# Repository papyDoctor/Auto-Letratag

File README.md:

# Auto-Letratag

**📖 Build log, photos and videos: [papydoctor.github.io/Auto-Letratag](https://papydoctor.github.io/Auto-Letratag/)**

Also published on [Hackster.io](https://www.hackster.io/papyDoctor/auto-letratag-batch-printing-and-cutting-of-numbered-labels-c18717).

This project is a reverse engineering of the LetraTag LT‑100H, a 12 mm label printer. I built it for my own needs, to automate label making. I have thousands of 12 mm labels to print with increasing numbers, and I no longer wanted to do it by hand on the LT‑100H. As far as I know, there is no device that can print series of 12 mm labels with automatic cutting.

The system connects to a PC through its USB‑C port, which both powers the printer and controls it.

In practice, this project needs an LT‑100H and:

| Function | Part |
|---|---|
| Microcontroller | Waveshare RP2350‑Zero (RP2350A, USB‑C) |
| Motor | NEMA 17 17HS19‑1684D, directly on the original roller |
| Motor driver | Watterott TMC2209 SilentStepStick, 1/32 microstepping, stealthChop, about 0.4 A |
| Head and motor supply | TPS61089 boost converter, 5 V → 6.5 V, enabled by the firmware |
| Head driver | 4 × TLC5916 in a daisy chain, used as switches: the head runs at constant voltage (about 73 mA per dot) |
| Cutter | HS-5085MG servo |
| User interface | 2 buttons, VBUS and head rail sensing, input for an optional thermistor |

All of the original electronics are replaced by a custom board. The thermal print head, the drive roller, the blade and the tape cassettes come from the original machine. The board drives a stepper motor coupled directly to the roller and cuts the tape with a servo. A terminal program lays out the text and sends it to the printer.

Terminal features:

- **Numbered series.** The template `BOX-{n:03}` from 1 to 20 gives BOX-001, BOX-002, … BOX-020.
- **Chained labels.** Labels are printed back to back. Each one is cut when its boundary reaches the blade, so no tape is wasted between labels.
- **Continuous printing** at about 30 mm/s: the motor does not stop between lines.
- **Full-height text** using all 30 dots of the head, on one or more lines, in any TrueType font.
- **Saved templates** to quickly reuse frequent texts.

The 3D model of the assembly is in [`mechanical/ASSY.glb`](mechanical/ASSY.glb).

> This is a personal project, I'm not affiliated with Dymo. Dymo and LetraTag are trademarks of their respective owners.

## Specifications

| | |
|---|---|
| Print head | 30 dots, 0.15 mm pitch (about 170 dpi), 4.5 mm print height |
| Speed | about 30 mm/s in continuous mode (5 ms per full line) |
| Cutting | automatic, servo-driven, head-to-blade distance adjustable without recompiling |
| Power | USB‑C 5 V (designed for a USB‑C port that supplies up to 3 A) |
| Link | USB serial port, text protocol |

## V3 board

KiCad 10, 4-layer, 70 × 60 mm ([`hardware/V3`](hardware/V3), schematic as [PDF](hardware/V3/letratag-schematic.pdf)).

**Head drive.** The head and motor rail (+6V5 in the schematic) is set to 6.5 V. Each TLC5916 output only switches its dot on and off; its current limit, about 105 mA with R1–R4 = 180 Ω, only protects the head. The board was first built to drive the dots at constant current (7.5 V rail, 69 mA per dot). That was a mistake: the resistance of a dot rises as it wears, and at constant current its power (I²R) rises with it, so a worn dot runs hotter and hotter until it burns out. At constant voltage, its power (V²/R) goes down instead.

**Heating time.** Each dot heats for 1.5 ms, a constant in the firmware (`HEAT_US`), not a setting. At 6.5 V, 1.5 ms already prints solid black and 1 ms prints grey; longer pulses only wear the head.

**Current budget.** Heating all 30 dots at once would draw about 3.2 A from USB. The firmware therefore heats each line in groups of 10 dots. The groups are interleaved, so the text stays straight while the tape moves.

**Power sequencing.** The switched +5 V rail comes up first, then the head and motor rail, then the motor driver. Everything is switched off at the end of a series, or after one minute without activity.

[`hardware/V1`](hardware/V1) and [`hardware/V2`](hardware/V2) are earlier versions, built around a XIAO RP2350 and the original DC motor.

## Firmware

[`firmware/letratag_v3/letratag_v3.ino`](firmware/letratag_v3/letratag_v3.ino), written in Arduino.

To build it, install Earle Philhower's [arduino‑pico](https://github.com/earlephilhower/arduino-pico) core in the Arduino IDE and select the **Waveshare RP2350 Zero** board. The `Servo` and `EEPROM` libraries come with the core. From the command line:

```sh
arduino-cli compile --fqbn rp2040:rp2040:waveshare_rp2350_zero firmware/letratag_v3
```

The folder also contains two other programs:
- [`firmware/test_v3`](firmware/test_v3): a bring-up sketch for the V3 board, to test the power rails, motor, servo and head one at a time;
- [`firmware/letratag`](firmware/letratag): the firmware for the earlier versions.

### Console

The USB serial port runs at 115200 baud, with newline line endings. `help` (or any unknown command) lists all commands.

| Command | Action |
|---|---|
| `blocks`, `ruler`, `square`, `line <dot>`, `dots` | test labels (`dots`: staircase to find a dead dot) |
| `blade <mm>` | distance from the dot line to the blade (saved in flash) |
| `margin <mm>` | blank space before and after the text (saved in flash) |
| `group <n>` | number of dots heated at the same time (saved in flash) |
| `calib` | prints a thin bar and cuts through its middle if `blade` is right |
| `feed <mm>`, `cut`, `flush` | feed the tape; cut; feed out and cut what has been printed |
| `status`, `off` | voltages and settings; switch off all power rails |

**Buttons:**
- **A**, held: feeds the tape;
- **B**: cuts what has been printed;
- **either button** stops a print in progress.

### Cutter calibration

Do this once, then again whenever the cutter mechanism changes:

1. Type `calib`. The firmware prints a thin bar and cuts where its middle should be.
2. Look for the bar:
   - **on the piece that came out**, x mm from the edge: type `blade <current value − x>`;
   - **on the tape still in the machine**, x mm from the edge: type `blade <current value + x>`.
3. Repeat until the cut goes through the bar.

The cutter servo travel is set in the firmware by `SERVO_REST_US` (blade retracted) and `SERVO_CUT_US` (full cut). Measure it on each mechanism: beyond these limits, the servo pushes against its end stops.

### Protocol

One text command per line:

```
PC → INFO                     PC ← INFO first=1 dots=30 pitch_um=150 max_lines=4000 cut=2
PC → IMG <n> [c] [k]          PC ← READY <n>
PC → L <hex>   (n times)      PC ← P <i>/<n> … SPEED … VOLTAGES … DONE
PC → FLUSH                    PC ← DONE
```

- **`L` lines:** each line is a 30-bit word in hexadecimal; bit 0 is the top dot of the label.
- **`c`:** `1` (default) for continuous printing, `0` to stop the motor at each line.
- **`k`:** `1` (default) to feed out and cut the label, `0` if another label follows. In that case, the cut happens while the next label is printing.
- **`ERR <message>`** reports an error.

## Terminal program

[`software`](software) is a terminal application written in Rust with ratatui.

```sh
cd software
cargo build --release
./target/release/letratag
```

The program finds the board on USB by itself. Close the Arduino IDE serial monitor first, otherwise the port is busy.

| Option | |
|---|---|
| `--port <port>` | serial port, if automatic detection fails |
| `--font <file.ttf>` | font (default: macOS Arial Bold) |
| `--width <factor>` | character width, from 1 to 2 (default 1.08, matching an original Dymo label) |
| `--templates <file>` | saved templates file (default: `~/.config/letratag/templates.txt`) |
| `--mirror` | prints the text mirrored |

**Fields:**
- **Template**: the text. `{n}` or `{n:03}` is replaced by the number, and `|` starts a new line.
- **Start** and **End**: the numbers of the series.

A preview shows the label before printing.

| Key | |
|---|---|
| Ctrl‑P or F5 | print the series |
| Ctrl‑N | new line in the template |
| Ctrl‑S / Ctrl‑O | save the template / pick a saved template |
| Ctrl‑A | continuous / stop at each line |
| Esc | stop after the current label, or quit |

Saved templates are stored in a plain text file, one per line, which can also be edited by hand.

## Repository layout

```
firmware/     V3 firmware, bring-up sketch, firmware for earlier versions
software/     PC program (Rust)
hardware/     V1, V2, V3 boards (KiCad)
mechanical/   3D assembly (ASSY.glb)
docs/         project web page (GitHub Pages)
Datasheets/   component datasheets
scripts/      helper tools
```

## License

Copyright (c) 2026 Olivier Monnom.

| | License |
|---|---|
| Software: `firmware/`, `software/`, `scripts/` | [MIT](LICENSE) |
| Hardware: `hardware/` (KiCad boards), `mechanical/` (3D parts) | [CERN-OHL-P v2](LICENSE-HARDWARE) |
| Documentation: `docs/` (text, photos, videos), this README | [CC BY 4.0](LICENSE-DOCS) |

Not covered by these licenses, and belonging to their manufacturers:
- the datasheets in `Datasheets/`;
- the vendor 3D models included in `mechanical/ASSY.glb`: stepper motor, servo, TMC2209 module.

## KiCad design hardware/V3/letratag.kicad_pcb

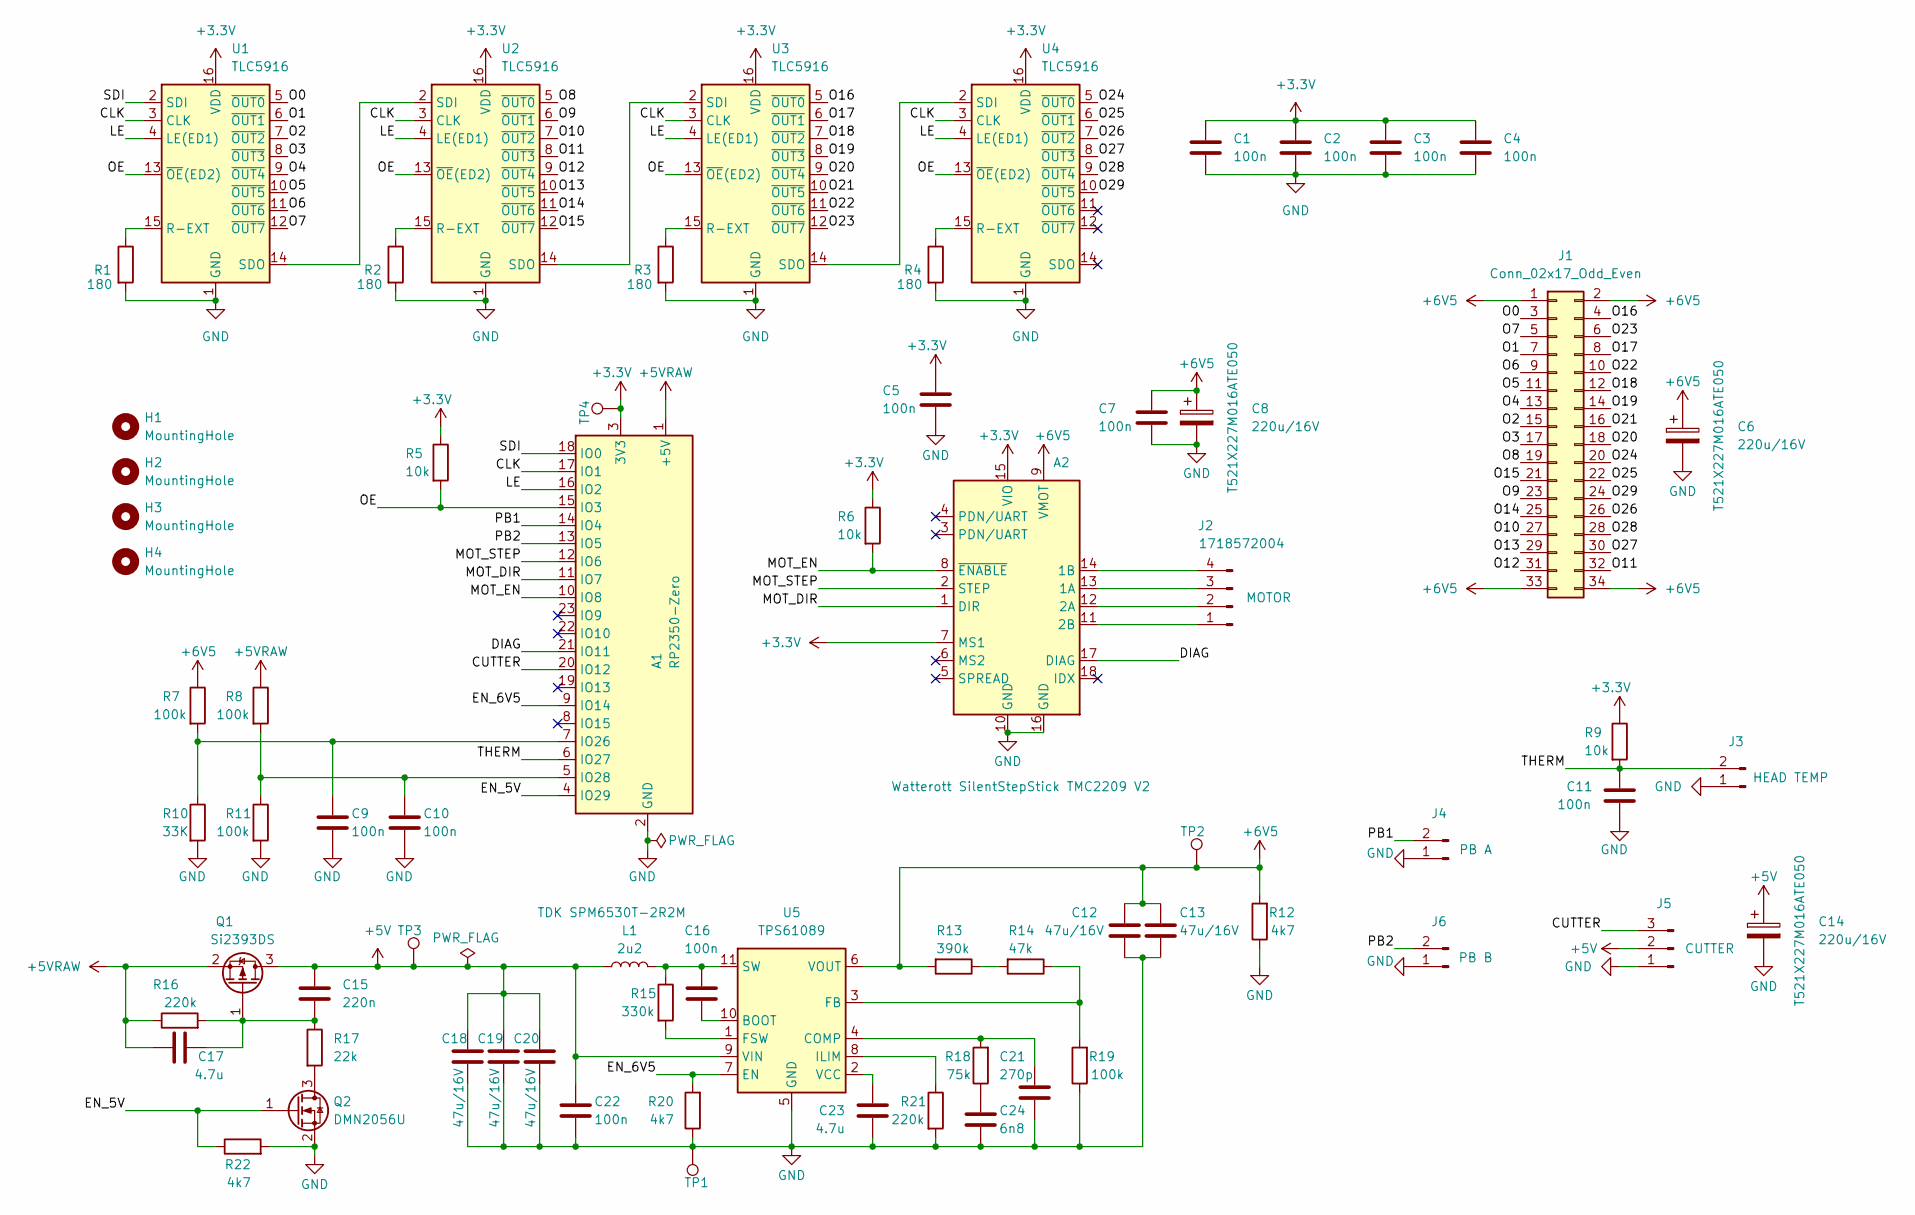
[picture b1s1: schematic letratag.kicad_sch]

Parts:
A1: RP2350-Zero; WAVESHARE-RP2350-ZERO
A2: Watterott SilentStepStick TMC2209 V2; Watterott_Breakout-16_15.2x20.3mm
C1, C2, C3, C4, C5, C7, C9, C10, C11, C16, C22: 100n; C_0603_1608Metric_Pad1.08x0.95mm_HandSolder
C6, C8, C14: 220u/16V; CP_EIA-7343-43_Kemet-X_HandSolder
C12, C13, C18, C19, C20: 47u/16V; C_1210_3225Metric_Pad1.33x2.70mm_HandSolder
C15: 220n; C_0603_1608Metric_Pad1.08x0.95mm_HandSolder
C17, C23: 4.7u; C_0603_1608Metric_Pad1.08x0.95mm_HandSolder
C21: 270p; C_0603_1608Metric_Pad1.08x0.95mm_HandSolder
C24: 6n8; C_0603_1608Metric_Pad1.08x0.95mm_HandSolder
H1, H2, H3, H4: MountingHole; MountingHole_3mm_Pad_Via
J1: Conn_02x17_Odd_Even; Samtec_EHF-117-01-L-D
J2: 1718572004; Molex_KK-254_RPC_1x04_P2.54mm_RA
J3: HEAD TEMP; JST_ZH_B2B-ZR_1x02_P1.50mm_Vertical
J4: PUSH BUTTON A; JST_ZH_B2B-ZR_1x02_P1.50mm_Vertical
J5: CUTTER; PinHeader_1x03_P2.54mm_Vertical
J6: PUSH BUTTON B; JST_ZH_B2B-ZR_1x02_P1.50mm_Vertical
L1: 2u2; L_TDK_SMP6530
Q1: Si2393DS; SOT-23
Q2: DMN2056U; SOT-23
R1, R2, R3, R4: 180; R_1206_3216Metric_Pad1.30x1.75mm_HandSolder
R5, R6, R9: 10k; R_0603_1608Metric_Pad0.98x0.95mm_HandSolder
R7, R8, R11, R19: 100k; R_0603_1608Metric_Pad0.98x0.95mm_HandSolder
R10: 33K; R_0603_1608Metric_Pad0.98x0.95mm_HandSolder
R12, R20, R22: 4k7; R_0603_1608Metric_Pad0.98x0.95mm_HandSolder
R13: 390k; R_0603_1608Metric_Pad0.98x0.95mm_HandSolder
R14: 47k; R_0603_1608Metric_Pad0.98x0.95mm_HandSolder
R15: 330k; R_0603_1608Metric_Pad0.98x0.95mm_HandSolder
R16, R21: 220k; R_0603_1608Metric_Pad0.98x0.95mm_HandSolder
R17: 22k; R_0603_1608Metric_Pad0.98x0.95mm_HandSolder
R18: 75k; R_0603_1608Metric_Pad0.98x0.95mm_HandSolder
TP1, TP2, TP3, TP4: TestPoint; TestPoint_THTPad_D2.0mm_Drill1.0mm
U1, U2, U3, U4: TLC5916; SOP-16_3.9x9.9mm_P1.27mm
U5: TPS61089; Texas_VQFN-RNR0011A-11

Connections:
+3.3V: A1.3 (3V3), A2.7 (MS1), A2.15 (VIO), C1.1, C2.1, C3.1, C4.1, C5.1, R5.1, R6.1, R9.1, TP4.1 (1_1), U1.16 (VDD), U2.16 (VDD), U3.16 (VDD), U4.16 (VDD)
+5V: C14.1, C15.1, C18.1, C19.1, C20.1, C22.1, J5.2, L1.1, Q1.3 (D), TP3.1 (1_1), U5.9 (VIN)
+5VRAW: A1.1 (+5V), C17.1, Q1.2 (S), R8.1, R16.1
+6V5: A2.9 (VMOT), C6.1, C7.1, C8.1, C12.1, C13.1, J1.1, J1.2, J1.33, J1.34, R7.1, R12.2, R13.2, TP2.1 (1_1), U5.6 (VOUT)
/CLK: A1.17 (IO1), U1.3 (CLK), U2.3 (CLK), U3.3 (CLK), U4.3 (CLK)
/CUTTER: A1.20 (IO12), J5.3
/DIAG: A1.21 (IO11), A2.17 (DIAG)
/EN_5V: A1.4 (IO29), Q2.1 (G), R22.1
/EN_6V5: A1.9 (IO14), R20.2, U5.7 (EN)
/LE: A1.16 (IO2), U1.4 (LE(ED1)), U2.4 (LE(ED1)), U3.4 (LE(ED1)), U4.4 (LE(ED1))
/MOT_DIR: A1.11 (IO7), A2.1 (DIR)
/MOT_EN: A1.10 (IO8), A2.8 (~ENABLE), R6.2
/MOT_STEP: A1.12 (IO6), A2.2 (STEP)
/O0: J1.3, U1.5 (~OUT0)
/O1: J1.7, U1.6 (~OUT1)
/O2: J1.15, U1.7 (~OUT2)
/O3: J1.17, U1.8 (~OUT3)
/O4: J1.13, U1.9 (~OUT4)
/O5: J1.11, U1.10 (~OUT5)
/O6: J1.9, U1.11 (~OUT6)
/O7: J1.5, U1.12 (~OUT7)
/O8: J1.19, U2.5 (~OUT0)
/O9: J1.23, U2.6 (~OUT1)
/O10: J1.27, U2.7 (~OUT2)
/O11: J1.32, U2.8 (~OUT3)
/O12: J1.31, U2.9 (~OUT4)
/O13: J1.29, U2.10 (~OUT5)
/O14: J1.25, U2.11 (~OUT6)
/O15: J1.21, U2.12 (~OUT7)
/O16: J1.4, U3.5 (~OUT0)
/O17: J1.8, U3.6 (~OUT1)
/O18: J1.12, U3.7 (~OUT2)
/O19: J1.14, U3.8 (~OUT3)
/O20: J1.18, U3.9 (~OUT4)
/O21: J1.16, U3.10 (~OUT5)
/O22: J1.10, U3.11 (~OUT6)
/O23: J1.6, U3.12 (~OUT7)
/O24: J1.20, U4.5 (~OUT0)
/O25: J1.22, U4.6 (~OUT1)
/O26: J1.26, U4.7 (~OUT2)
/O27: J1.30, U4.8 (~OUT3)
/O28: J1.28, U4.9 (~OUT4)
/O29: J1.24, U4.10 (~OUT5)
/OE: A1.15 (IO3), R5.2, U1.13 (~OE(ED2)), U2.13 (~OE(ED2)), U3.13 (~OE(ED2)), U4.13 (~OE(ED2))
/PB1: A1.14 (IO4), J4.2
/PB2: A1.13 (IO5), J6.2
/SDI: A1.18 (IO0), U1.2 (SDI)
/THERM: A1.6 (IO27), C11.1, J3.2, R9.2
GND: A1.2 (GND), A2.10 (GND), A2.16 (GND), C1.2, C2.2, C3.2, C4.2, C5.2, C6.2, C7.2, C8.2, C9.2, C10.2, C11.2, C12.2, C13.2, C14.2, C18.2, C19.2, C20.2, C21.2, C22.2, C23.1, C24.2, J3.1, J4.1, J5.1, J6.1, Q2.2 (S), R1.2, R2.2, R3.2, R4.2, R10.2, R11.2, R12.1, R19.1, R20.1, R21.2, R22.2, TP1.1 (1_1), U1.1 (GND), U2.1 (GND), U3.1 (GND), U4.1 (GND), U5.5 (GND)
unnamed: A1.7 (IO26), C9.1, R7.2, R10.1
unnamed: A1.5 (IO28), C10.1, R8.2, R11.1
unnamed: A2.13 (1A), J2.3
unnamed: A2.14 (1B), J2.4
unnamed: A2.12 (2A), J2.2
unnamed: A2.11 (2B), J2.1
unnamed: C24.1, R18.1
unnamed: C15.2, C17.2, Q1.1 (G), R16.2, R17.1
unnamed: Q2.3 (D), R17.2
unnamed: R13.1, R14.2
unnamed: R1.1, U1.15 (R-EXT)
unnamed: U1.14 (SDO), U2.2 (SDI)
unnamed: R2.1, U2.15 (R-EXT)
unnamed: U2.14 (SDO), U3.2 (SDI)
unnamed: R3.1, U3.15 (R-EXT)
unnamed: U3.14 (SDO), U4.2 (SDI)
unnamed: R4.1, U4.15 (R-EXT)
unnamed: C16.2, U5.10 (BOOT)
unnamed: C21.1, R18.2, U5.4 (COMP)
unnamed: R14.1, R19.2, U5.3 (FB)
unnamed: R15.2, U5.1 (FSW)
unnamed: R21.1, U5.8 (ILIM)
unnamed: C16.1, L1.2, R15.1, U5.11 (SW)
unnamed: C23.2, U5.2 (VCC)

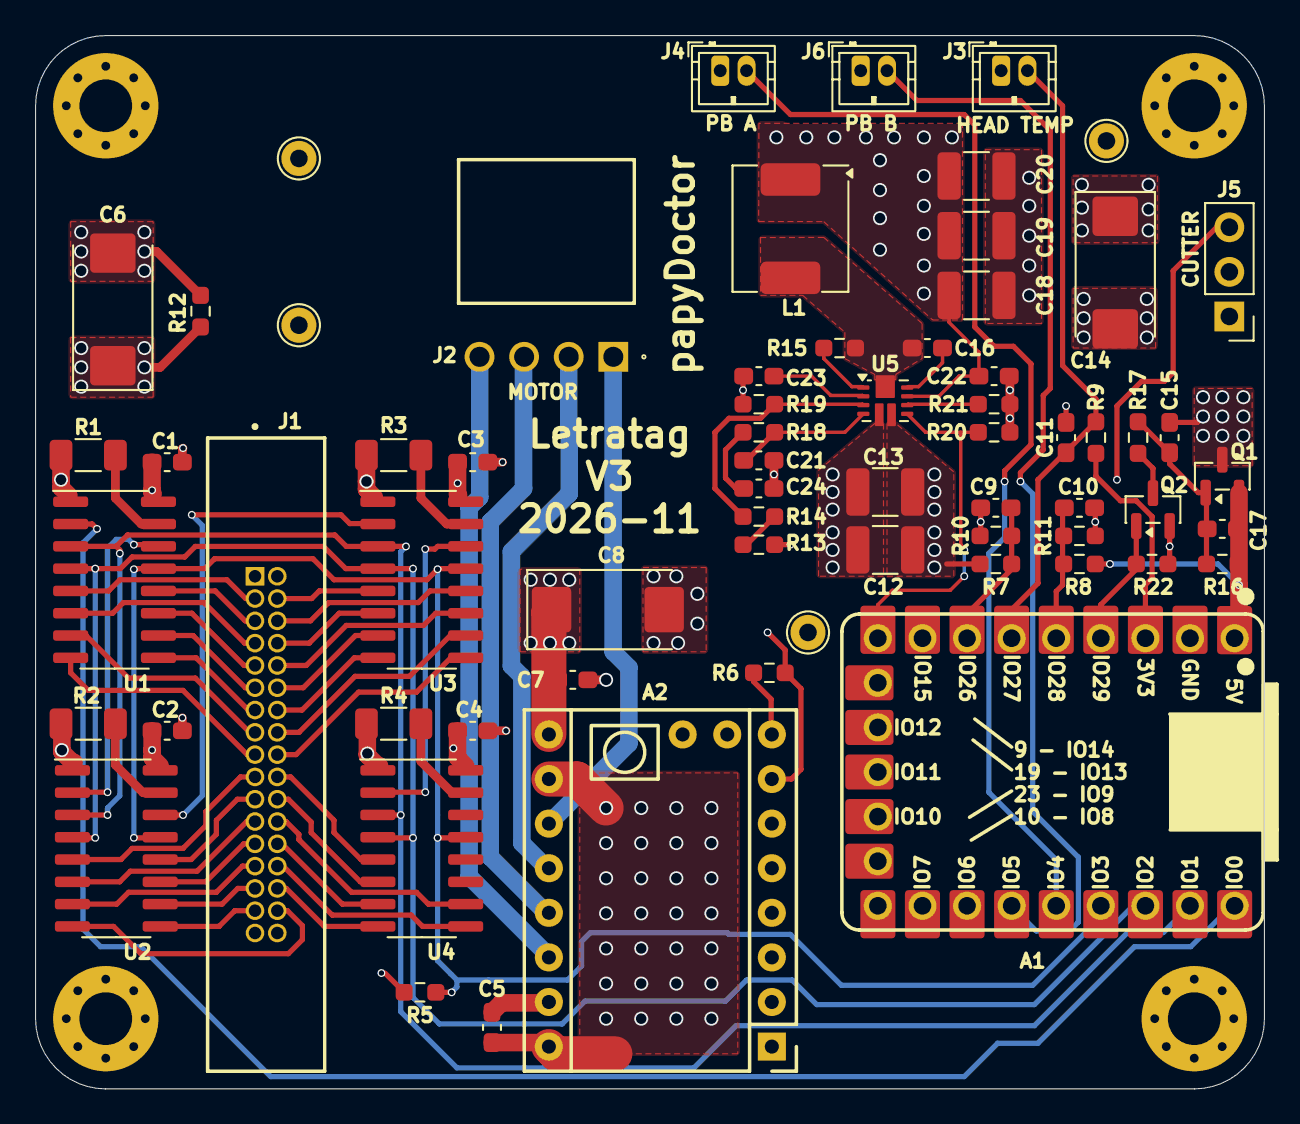
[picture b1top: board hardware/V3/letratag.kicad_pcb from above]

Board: 4 copper layers, 70.0 x 60.0 mm, 70 parts (0 on the bottom side), 73 nets.

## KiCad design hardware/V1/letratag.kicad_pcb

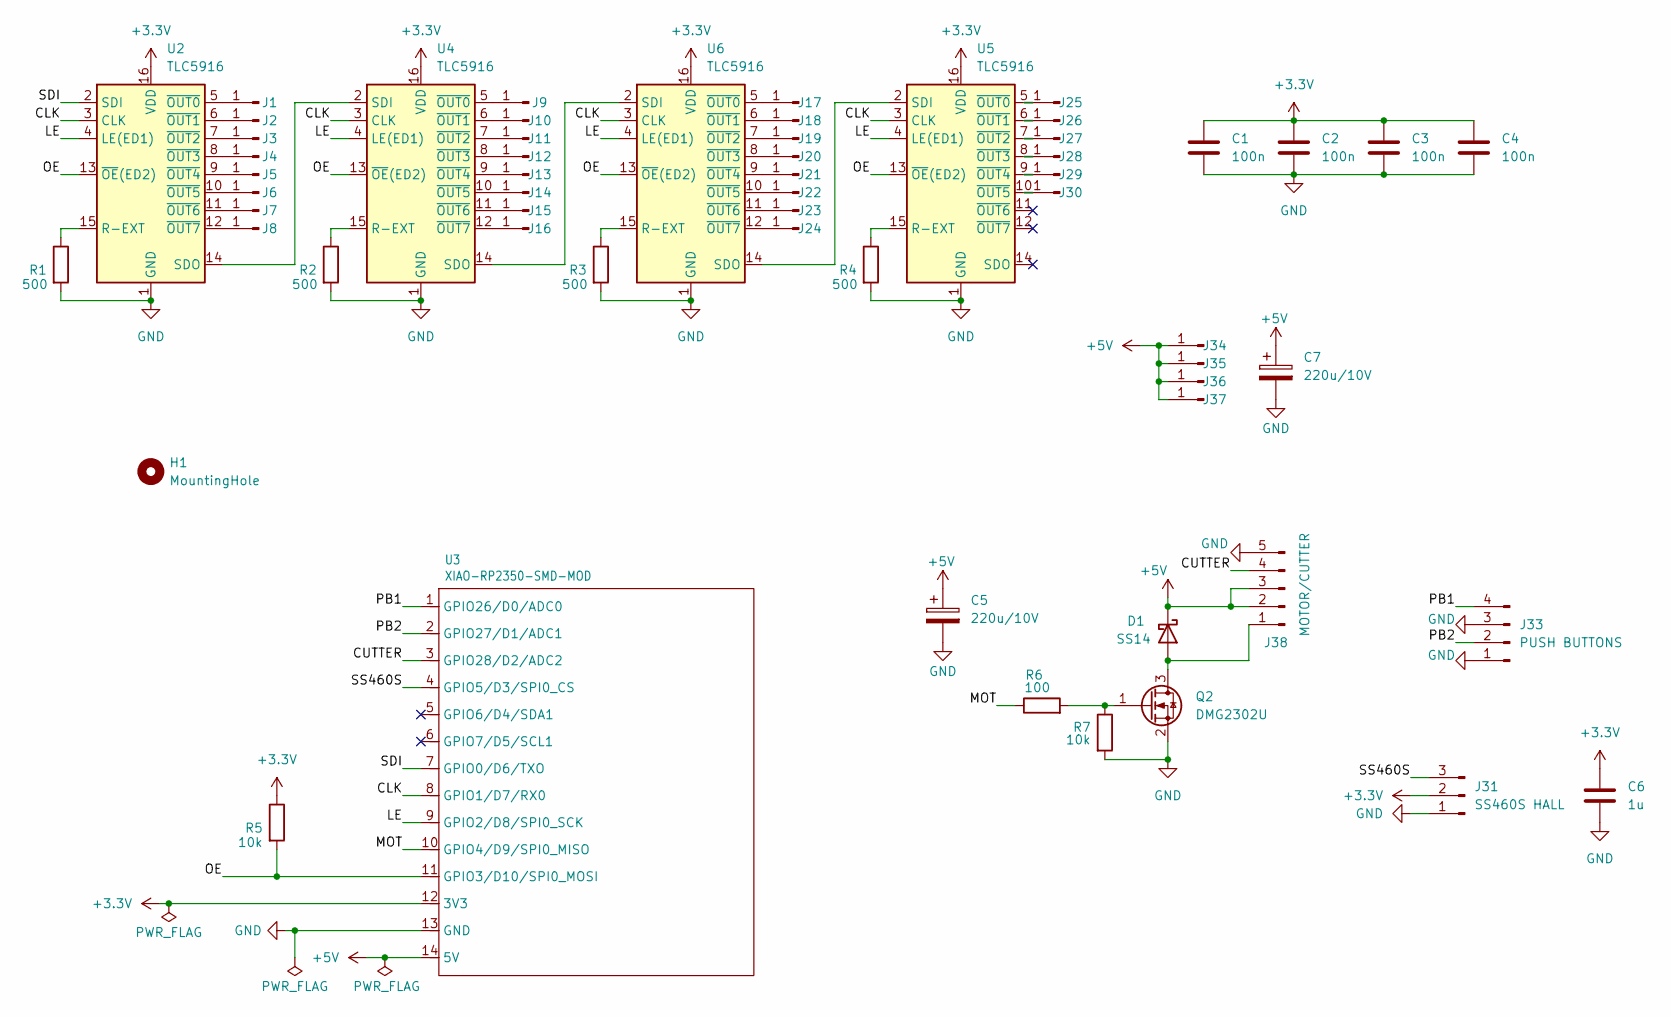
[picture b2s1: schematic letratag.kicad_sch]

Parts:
C1, C2, C3, C4: 100n; C_0603_1608Metric_Pad1.08x0.95mm_HandSolder
C5, C7: 220u/10V; CP_EIA-7343-31_Kemet-D_HandSolder
C6: 1u; C_0603_1608Metric_Pad1.08x0.95mm_HandSolder
D1: SS14; D_SMA
H1: MountingHole; MountingHole_2.5mm
J1, J2, J3, J4, J5, J6, J7, J8, J9, J10, J11, J12, J13, J14, J15, J16, J17, J18, J19, J20, J21, J22, J23, J24, J25, J26, J27, J28, J29, J30, J34, J35, J36, J37: Conn_01x01_Pin; PIN_RECT_0.5x4mm
J31: SS460S HALL; JST_ZH_B3B-ZR_1x03_P1.50mm_Vertical
J33: PUSH BUTTONS; JST_ZH_B4B-ZR_1x04_P1.50mm_Vertical
J38: MOTOR/CUTTER; JST_ZH_B5B-ZR_1x05_P1.50mm_Vertical
Q2: DMG2302U; SOT-23
R1, R2, R3, R4: 500; R_0603_1608Metric_Pad0.98x0.95mm_HandSolder
R5, R7: 10k; R_0603_1608Metric_Pad0.98x0.95mm_HandSolder
R6: 100; R_0603_1608Metric_Pad0.98x0.95mm_HandSolder
U2, U4, U5, U6: TLC5916; SOP-16_3.9x9.9mm_P1.27mm
U3: XIAO-RP2350-SMD-MOD; XIAO-RP2350-SMD

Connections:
+3.3V: C1.1, C2.1, C3.1, C4.1, C6.1, J31.2, R5.1, U2.16 (VDD), U3.12 (3V3), U4.16 (VDD), U5.16 (VDD), U6.16 (VDD)
+5V: C5.1, C7.1, D1.1 (K), J34.1 (Pin_1_1), J35.1 (Pin_1_1), J36.1 (Pin_1_1), J37.1 (Pin_1_1), J38.2, J38.3, U3.14 (5V)
/CLK: U2.3 (CLK), U3.8 (GPIO1/D7/RX0), U4.3 (CLK), U5.3 (CLK), U6.3 (CLK)
/CUTTER: J38.4, U3.3 (GPIO28/D2/ADC2)
/LE: U2.4 (LE(ED1)), U3.9 (GPIO2/D8/SPI0_SCK), U4.4 (LE(ED1)), U5.4 (LE(ED1)), U6.4 (LE(ED1))
/MOT: R6.1, U3.10 (GPIO4/D9/SPI0_MISO)
/OE: R5.2, U2.13 (~OE(ED2)), U3.11 (GPIO3/D10/SPI0_MOSI), U4.13 (~OE(ED2)), U5.13 (~OE(ED2)), U6.13 (~OE(ED2))
/PB1: J33.4, U3.1 (GPIO26/D0/ADC0)
/PB2: J33.2, U3.2 (GPIO27/D1/ADC1)
/SDI: U2.2 (SDI), U3.7 (GPIO0/D6/TXO)
/SS460S: J31.3, U3.4 (GPIO5/D3/SPI0_CS)
GND: C1.2, C2.2, C3.2, C4.2, C5.2, C6.2, C7.2, J31.1, J33.1, J33.3, J38.5, Q2.2 (S), R1.2, R2.2, R3.2, R4.2, R7.2, U2.1 (GND), U3.13 (GND), U4.1 (GND), U5.1 (GND), U6.1 (GND)
unnamed: D1.2 (A), J38.1, Q2.3 (D)
unnamed: J1.1 (Pin_1_1), U2.5 (~OUT0)
unnamed: J2.1 (Pin_1_1), U2.6 (~OUT1)
unnamed: J3.1 (Pin_1_1), U2.7 (~OUT2)
unnamed: J4.1 (Pin_1_1), U2.8 (~OUT3)
unnamed: J5.1 (Pin_1_1), U2.9 (~OUT4)
unnamed: J6.1 (Pin_1_1), U2.10 (~OUT5)
unnamed: J7.1 (Pin_1_1), U2.11 (~OUT6)
unnamed: J8.1 (Pin_1_1), U2.12 (~OUT7)
unnamed: J9.1 (Pin_1_1), U4.5 (~OUT0)
unnamed: J10.1 (Pin_1_1), U4.6 (~OUT1)
unnamed: J11.1 (Pin_1_1), U4.7 (~OUT2)
unnamed: J12.1 (Pin_1_1), U4.8 (~OUT3)
unnamed: J13.1 (Pin_1_1), U4.9 (~OUT4)
unnamed: J14.1 (Pin_1_1), U4.10 (~OUT5)
unnamed: J15.1 (Pin_1_1), U4.11 (~OUT6)
unnamed: J16.1 (Pin_1_1), U4.12 (~OUT7)
unnamed: J17.1 (Pin_1_1), U6.5 (~OUT0)
unnamed: J18.1 (Pin_1_1), U6.6 (~OUT1)
unnamed: J19.1 (Pin_1_1), U6.7 (~OUT2)
unnamed: J20.1 (Pin_1_1), U6.8 (~OUT3)
unnamed: J21.1 (Pin_1_1), U6.9 (~OUT4)
unnamed: J22.1 (Pin_1_1), U6.10 (~OUT5)
unnamed: J23.1 (Pin_1_1), U6.11 (~OUT6)
unnamed: J24.1 (Pin_1_1), U6.12 (~OUT7)
unnamed: J25.1 (Pin_1_1), U5.5 (~OUT0)
unnamed: J26.1 (Pin_1_1), U5.6 (~OUT1)
unnamed: J27.1 (Pin_1_1), U5.7 (~OUT2)
unnamed: J28.1 (Pin_1_1), U5.8 (~OUT3)
unnamed: J29.1 (Pin_1_1), U5.9 (~OUT4)
unnamed: J30.1 (Pin_1_1), U5.10 (~OUT5)
unnamed: Q2.1 (G), R6.2, R7.1
unnamed: R1.1, U2.15 (R-EXT)
unnamed: U2.14 (SDO), U4.2 (SDI)
unnamed: R2.1, U4.15 (R-EXT)
unnamed: U4.14 (SDO), U6.2 (SDI)
unnamed: R4.1, U5.15 (R-EXT)
unnamed: U5.2 (SDI), U6.14 (SDO)
unnamed: R3.1, U6.15 (R-EXT)

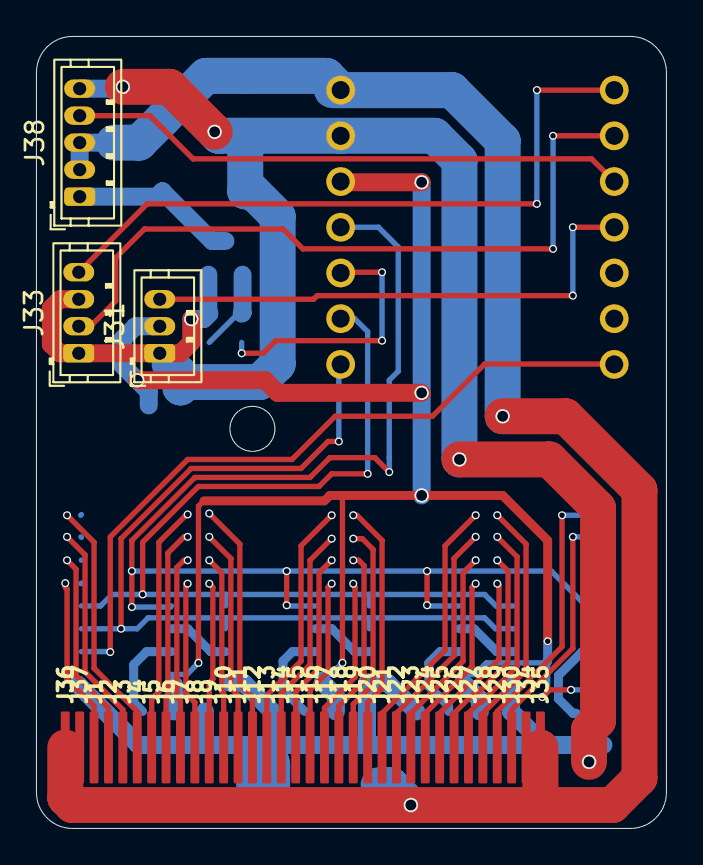
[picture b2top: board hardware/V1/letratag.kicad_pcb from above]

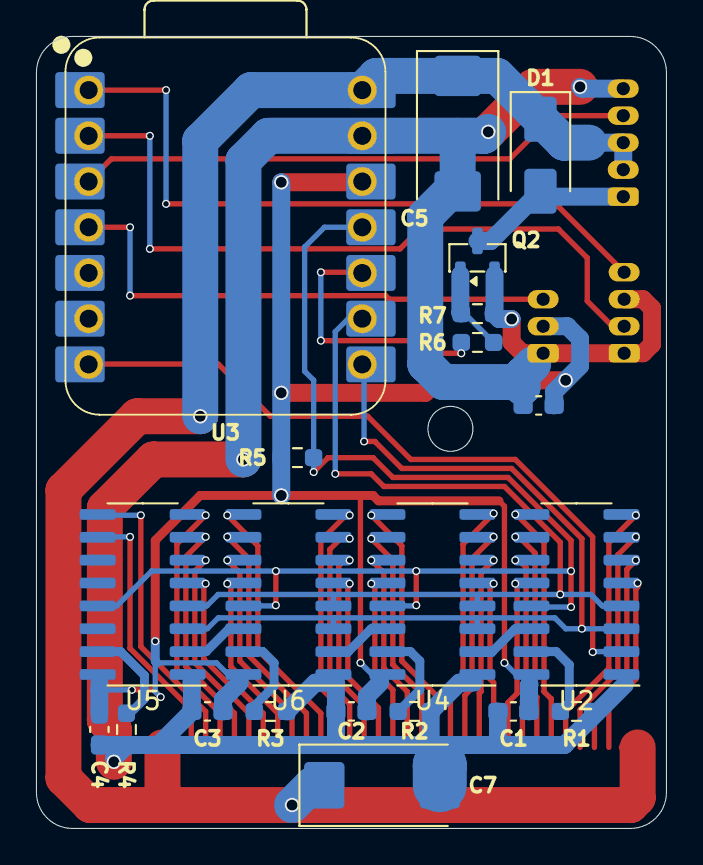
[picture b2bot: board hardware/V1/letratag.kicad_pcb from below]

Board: 2 copper layers, 35.0 x 44.0 mm, 59 parts (21 on the bottom side), 51 nets.

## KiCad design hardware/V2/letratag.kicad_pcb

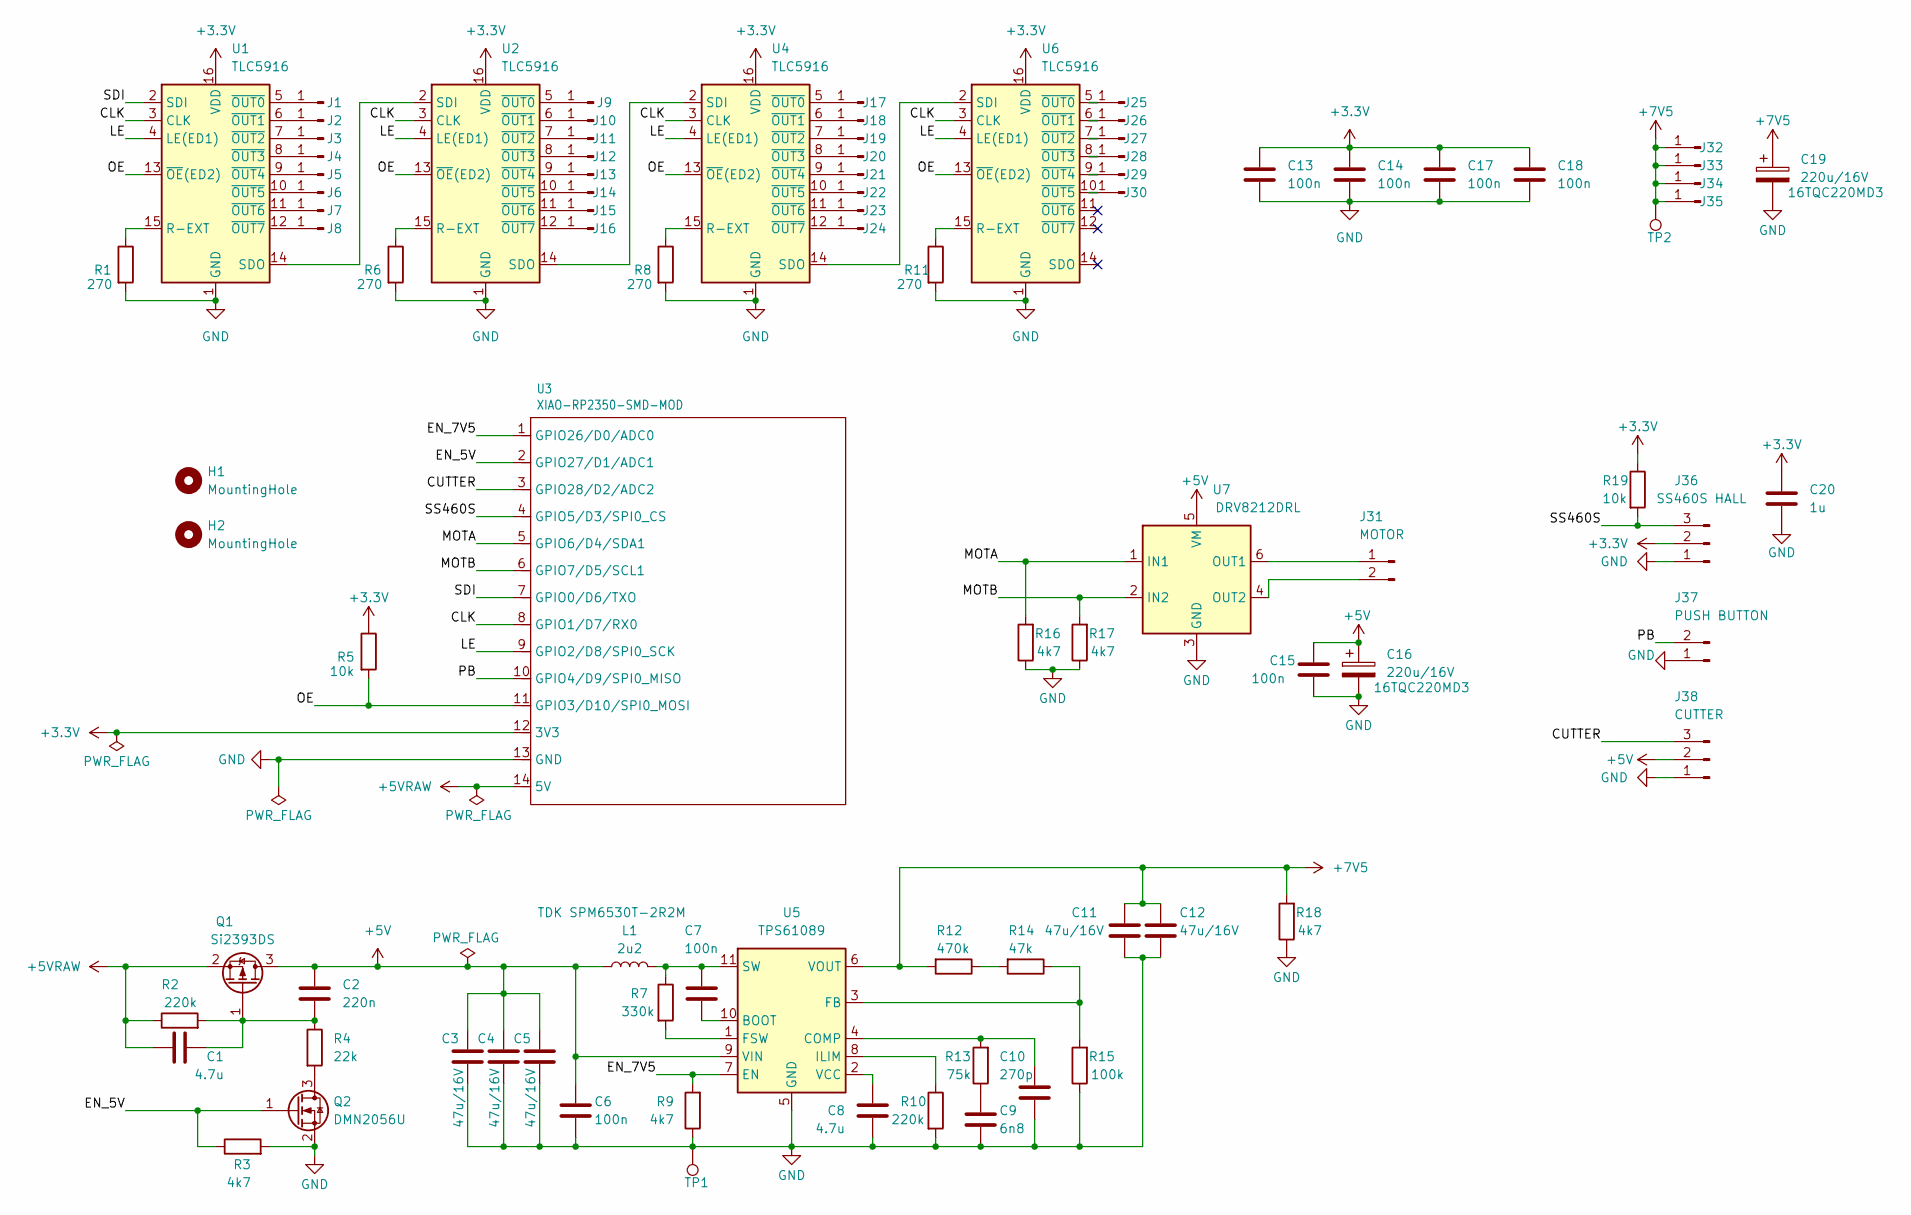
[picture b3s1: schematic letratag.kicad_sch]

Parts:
C1, C8: 4.7u; C_0603_1608Metric_Pad1.08x0.95mm_HandSolder
C2: 220n; C_0603_1608Metric_Pad1.08x0.95mm_HandSolder
C3, C4, C5, C11, C12: 47u/16V; C_1210_3225Metric_Pad1.33x2.70mm_HandSolder
C6, C7, C13, C14, C15, C17, C18: 100n; C_0603_1608Metric_Pad1.08x0.95mm_HandSolder
C9: 6n8; C_0603_1608Metric_Pad1.08x0.95mm_HandSolder
C10: 270p; C_0603_1608Metric_Pad1.08x0.95mm_HandSolder
C16, C19: 220u/16V; CP_EIA-7360-38_Kemet-E_Pad2.25x4.25mm_HandSolder
C20: 1u; C_0603_1608Metric_Pad1.08x0.95mm_HandSolder
H1, H2: MountingHole; MountingHole_2.5mm
J1, J2, J3, J4, J5, J6, J7, J8, J9, J10, J11, J12, J13, J14, J15, J16, J17, J18, J19, J20, J21, J22, J23, J24, J25, J26, J27, J28, J29, J30, J32, J33, J34, J35: Conn_01x01_Pin; PIN_RECT_0.5x4mm
J31: MOTOR; JST_ZH_B2B-ZR_1x02_P1.50mm_Vertical
J36: SS460S HALL; JST_ZH_B3B-ZR_1x03_P1.50mm_Vertical
J37: PUSH BUTTON; JST_ZH_B2B-ZR_1x02_P1.50mm_Vertical
J38: CUTTER; JST_ZH_B3B-ZR_1x03_P1.50mm_Vertical
L1: 2u2; L_Taiyo-Yuden_NR-80xx_HandSoldering
Q1: Si2393DS; SOT-23
Q2: DMN2056U; SOT-23
R1, R6, R8, R11: 270; R_1206_3216Metric_Pad1.30x1.75mm_HandSolder
R2, R10: 220k; R_0603_1608Metric_Pad0.98x0.95mm_HandSolder
R3, R9, R16, R17, R18: 4k7; R_0603_1608Metric_Pad0.98x0.95mm_HandSolder
R4: 22k; R_0603_1608Metric_Pad0.98x0.95mm_HandSolder
R5, R19: 10k; R_0603_1608Metric_Pad0.98x0.95mm_HandSolder
R7: 330k; R_0603_1608Metric_Pad0.98x0.95mm_HandSolder
R12: 470k; R_0603_1608Metric_Pad0.98x0.95mm_HandSolder
R13: 75k; R_0603_1608Metric_Pad0.98x0.95mm_HandSolder
R14: 47k; R_0603_1608Metric_Pad0.98x0.95mm_HandSolder
R15: 100k; R_0603_1608Metric_Pad0.98x0.95mm_HandSolder
TP1: TestPoint; TestPoint_THTPad_D1.0mm_Drill0.5mm
TP2: TestPoint; TestPoint_Pad_D2.0mm
U1, U2, U4, U6: TLC5916; SOP-16_3.9x9.9mm_P1.27mm
U3: XIAO-RP2350-SMD-MOD; XIAO-RP2350-SMD
U5: TPS61089; Texas_VQFN-RNR0011A-11
U7: DRV8212DRL; SOT-563

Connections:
+3.3V: C13.1, C14.1, C17.1, C18.1, C20.1, J36.2, R5.1, R19.1, U1.16 (VDD), U2.16 (VDD), U3.12 (3V3), U4.16 (VDD), U6.16 (VDD)
+5V: C2.1, C3.1, C4.1, C5.1, C6.1, C15.1, C16.1, J38.2, L1.1, Q1.3 (D), U5.9 (VIN), U7.5 (VM)
+5VRAW: C1.1, Q1.2 (S), R2.1, U3.14 (5V)
+7V5: C11.1, C12.1, C19.1, J32.1 (Pin_1_1), J33.1 (Pin_1_1), J34.1 (Pin_1_1), J35.1 (Pin_1_1), R12.2, R18.2, TP2.1 (1_1), U5.6 (VOUT)
/CLK: U1.3 (CLK), U2.3 (CLK), U3.8 (GPIO1/D7/RX0), U4.3 (CLK), U6.3 (CLK)
/CUTTER: J38.3, U3.3 (GPIO28/D2/ADC2)
/EN_5V: Q2.1 (G), R3.1, U3.2 (GPIO27/D1/ADC1)
/EN_7V5: R9.2, U3.1 (GPIO26/D0/ADC0), U5.7 (EN)
/LE: U1.4 (LE(ED1)), U2.4 (LE(ED1)), U3.9 (GPIO2/D8/SPI0_SCK), U4.4 (LE(ED1)), U6.4 (LE(ED1))
/MOTA: R16.2, U3.5 (GPIO6/D4/SDA1), U7.1 (IN1)
/MOTB: R17.2, U3.6 (GPIO7/D5/SCL1), U7.2 (IN2)
/OE: R5.2, U1.13 (~OE(ED2)), U2.13 (~OE(ED2)), U3.11 (GPIO3/D10/SPI0_MOSI), U4.13 (~OE(ED2)), U6.13 (~OE(ED2))
/PB: J37.2, U3.10 (GPIO4/D9/SPI0_MISO)
/SDI: U1.2 (SDI), U3.7 (GPIO0/D6/TXO)
/SS460S: J36.3, R19.2, U3.4 (GPIO5/D3/SPI0_CS)
GND: C3.2, C4.2, C5.2, C6.2, C8.1, C9.2, C10.2, C11.2, C12.2, C13.2, C14.2, C15.2, C16.2, C17.2, C18.2, C19.2, C20.2, J36.1, J37.1, J38.1, Q2.2 (S), R1.2, R3.2, R6.2, R8.2, R9.1, R10.2, R11.2, R15.1, R16.1, R17.1, R18.1, TP1.1 (1_1), U1.1 (GND), U2.1 (GND), U3.13 (GND), U4.1 (GND), U5.5 (GND), U6.1 (GND), U7.3 (GND)
unnamed: C9.1, R13.1
unnamed: J1.1 (Pin_1_1), U1.5 (~OUT0)
unnamed: J2.1 (Pin_1_1), U1.6 (~OUT1)
unnamed: J3.1 (Pin_1_1), U1.7 (~OUT2)
unnamed: J4.1 (Pin_1_1), U1.8 (~OUT3)
unnamed: J5.1 (Pin_1_1), U1.9 (~OUT4)
unnamed: J6.1 (Pin_1_1), U1.10 (~OUT5)
unnamed: J7.1 (Pin_1_1), U1.11 (~OUT6)
unnamed: J8.1 (Pin_1_1), U1.12 (~OUT7)
unnamed: J9.1 (Pin_1_1), U2.5 (~OUT0)
unnamed: J10.1 (Pin_1_1), U2.6 (~OUT1)
unnamed: J11.1 (Pin_1_1), U2.7 (~OUT2)
unnamed: J12.1 (Pin_1_1), U2.8 (~OUT3)
unnamed: J13.1 (Pin_1_1), U2.9 (~OUT4)
unnamed: J14.1 (Pin_1_1), U2.10 (~OUT5)
unnamed: J15.1 (Pin_1_1), U2.11 (~OUT6)
unnamed: J16.1 (Pin_1_1), U2.12 (~OUT7)
unnamed: J17.1 (Pin_1_1), U4.5 (~OUT0)
unnamed: J18.1 (Pin_1_1), U4.6 (~OUT1)
unnamed: J19.1 (Pin_1_1), U4.7 (~OUT2)
unnamed: J20.1 (Pin_1_1), U4.8 (~OUT3)
unnamed: J21.1 (Pin_1_1), U4.9 (~OUT4)
unnamed: J22.1 (Pin_1_1), U4.10 (~OUT5)
unnamed: J23.1 (Pin_1_1), U4.11 (~OUT6)
unnamed: J24.1 (Pin_1_1), U4.12 (~OUT7)
unnamed: J25.1 (Pin_1_1), U6.5 (~OUT0)
unnamed: J26.1 (Pin_1_1), U6.6 (~OUT1)
unnamed: J27.1 (Pin_1_1), U6.7 (~OUT2)
unnamed: J28.1 (Pin_1_1), U6.8 (~OUT3)
unnamed: J29.1 (Pin_1_1), U6.9 (~OUT4)
unnamed: J30.1 (Pin_1_1), U6.10 (~OUT5)
unnamed: J31.1, U7.6 (OUT1)
unnamed: J31.2, U7.4 (OUT2)
unnamed: C1.2, C2.2, Q1.1 (G), R2.2, R4.1
unnamed: Q2.3 (D), R4.2
unnamed: R12.1, R14.2
unnamed: R1.1, U1.15 (R-EXT)
unnamed: U1.14 (SDO), U2.2 (SDI)
unnamed: R6.1, U2.15 (R-EXT)
unnamed: U2.14 (SDO), U4.2 (SDI)
unnamed: R8.1, U4.15 (R-EXT)
unnamed: U4.14 (SDO), U6.2 (SDI)
unnamed: C7.2, U5.10 (BOOT)
unnamed: C10.1, R13.2, U5.4 (COMP)
unnamed: R14.1, R15.2, U5.3 (FB)
unnamed: R7.2, U5.1 (FSW)
unnamed: R10.1, U5.8 (ILIM)
unnamed: C7.1, L1.2, R7.1, U5.11 (SW)
unnamed: C8.2, U5.2 (VCC)
unnamed: R11.1, U6.15 (R-EXT)

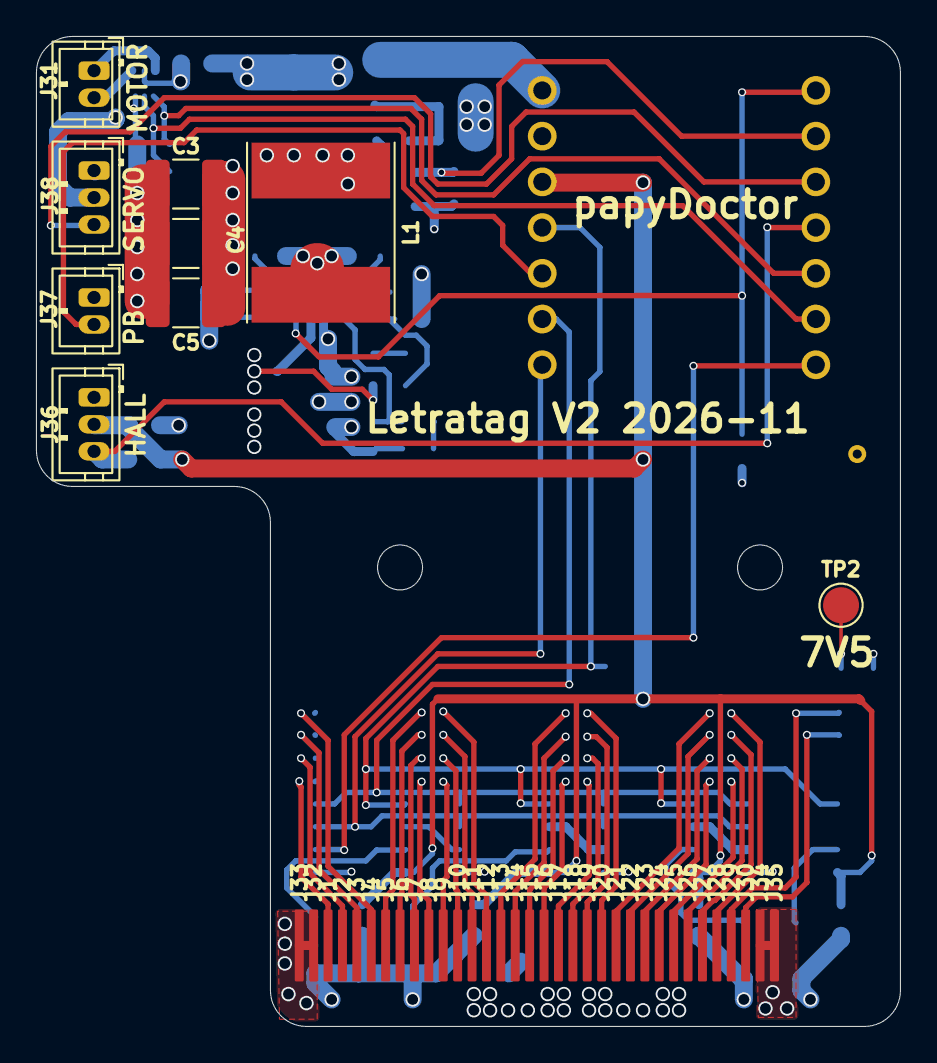
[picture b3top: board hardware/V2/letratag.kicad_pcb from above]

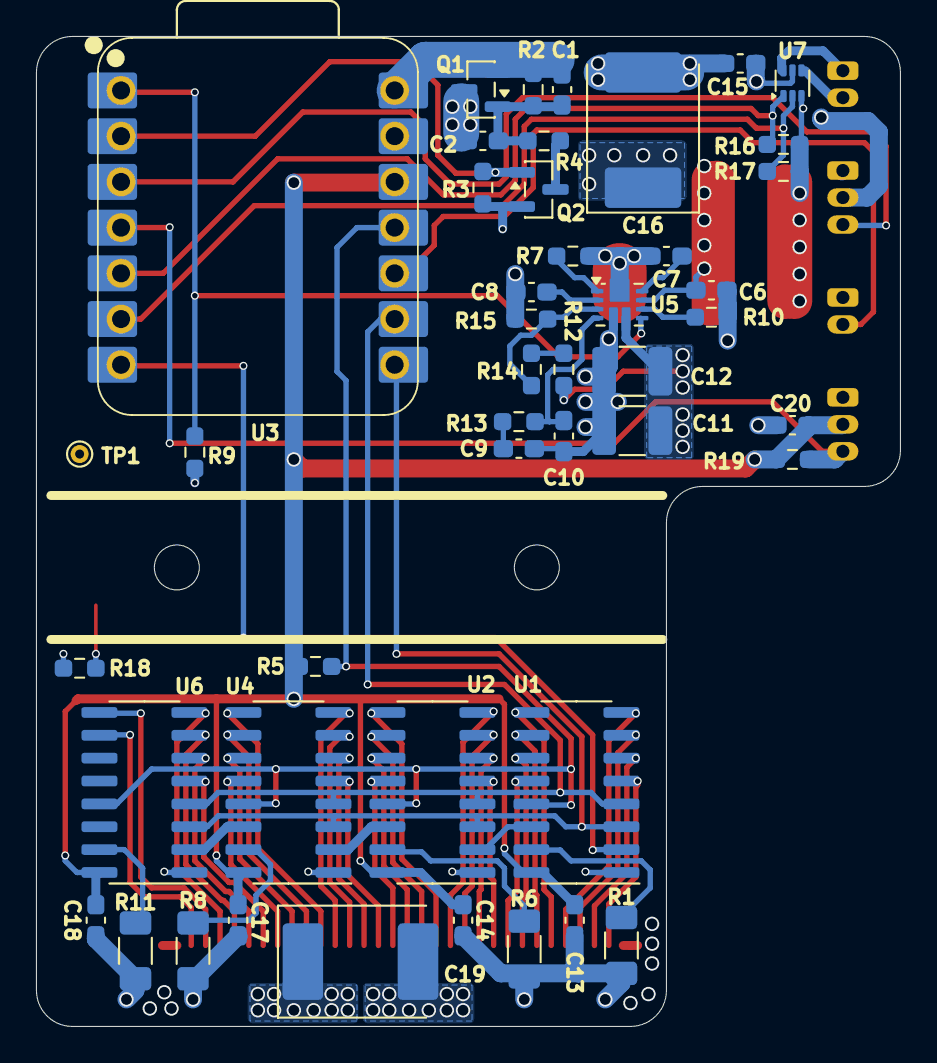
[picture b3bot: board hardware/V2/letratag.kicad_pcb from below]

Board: 4 copper layers, 48.0 x 55.0 mm, 91 parts (46 on the bottom side), 66 nets.

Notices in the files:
README.md:
Software license: MIT
Hardware license: CERN-OHL-P v2
Docs license: CC BY 4.0
